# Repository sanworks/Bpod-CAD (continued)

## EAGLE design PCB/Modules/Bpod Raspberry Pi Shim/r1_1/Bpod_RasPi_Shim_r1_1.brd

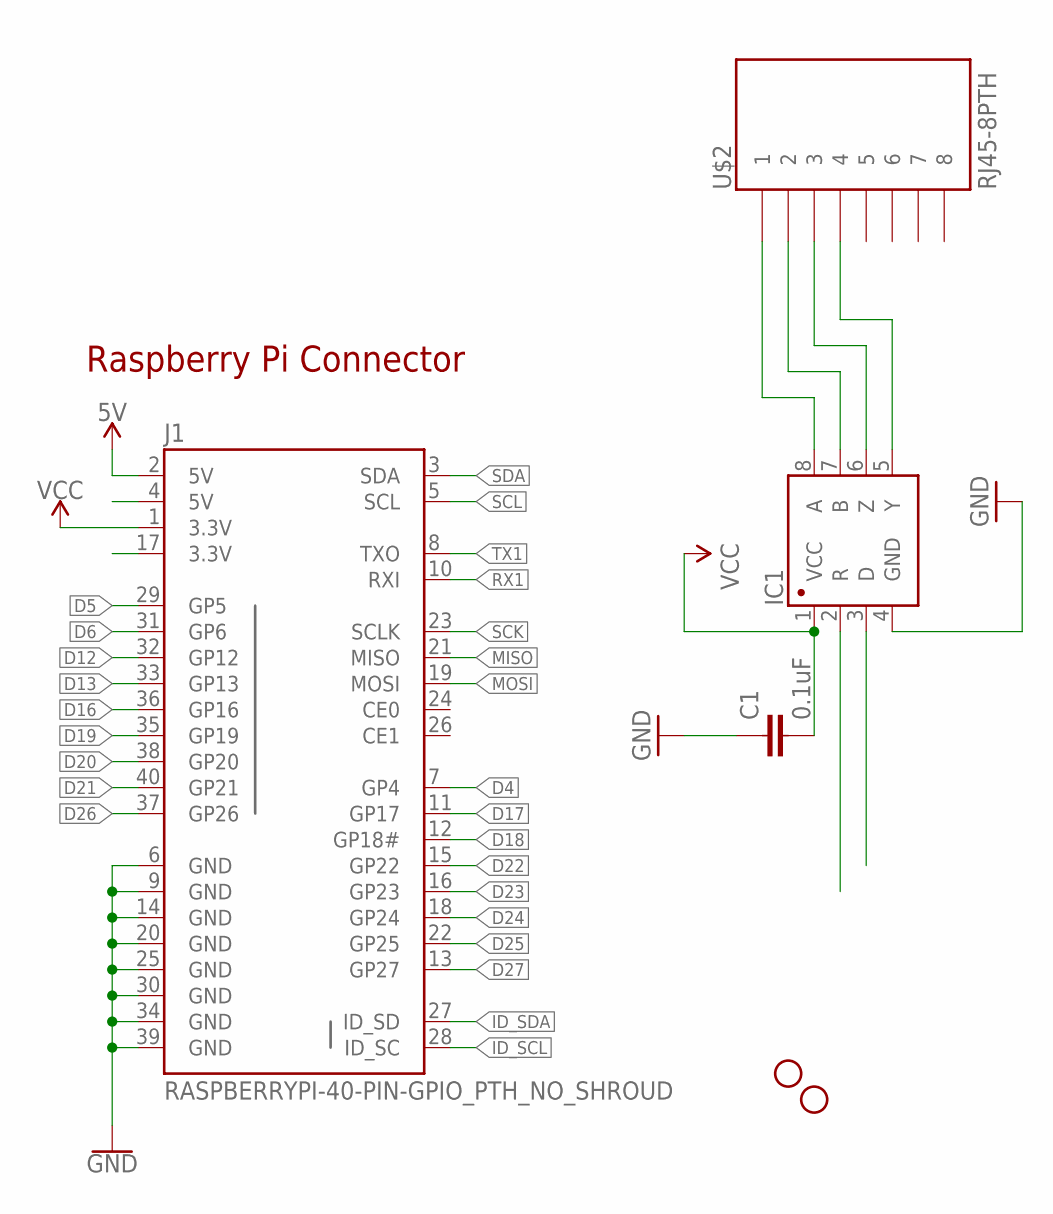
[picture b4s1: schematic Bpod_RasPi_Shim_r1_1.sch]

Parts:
C1: 0.1uF; 0805
H3, H4: STAND-OFFTIGHT; STAND-OFF-TIGHT
IC1: SN65HVD31DR; SO08
J1: RASPBERRYPI-40-PIN-GPIO_PTH_NO_SHROUD; 2X20
U$2: RJ45-8PTH; RJ45-8

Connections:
5V: J1.2 (5V)
D4: J1.7 (GP4)
D5: J1.29 (GP5)
D6: J1.31 (GP6)
D12: J1.32 (GP12)
D13: J1.33 (GP13)
D16: J1.36 (GP16)
D17: J1.11 (GP17)
D18: J1.12 (GP18#)
D19: J1.35 (GP19)
D20: J1.38 (GP20)
D21: J1.40 (GP21)
D22: J1.15 (GP22)
D23: J1.16 (GP23)
D24: J1.18 (GP24)
D25: J1.22 (GP25)
D26: J1.37 (GP26)
D27: J1.13 (GP27)
GND: C1.1, IC1.4 (GND), J1.6 (GND), J1.9 (GND), J1.14 (GND), J1.20 (GND), J1.25 (GND), J1.30 (GND), J1.34 (GND), J1.39 (GND)
ID_SCL: J1.28 (ID_SC)
ID_SDA: J1.27 (ID_SD)
MISO: J1.21 (MISO)
MOSI: J1.19 (MOSI)
unnamed: IC1.8 (A), U$2.1
unnamed: IC1.7 (B), U$2.2
unnamed: IC1.6 (Z), U$2.3
unnamed: IC1.5 (Y), U$2.4
RX1: IC1.2 (R), J1.10 (RXI)
SCK: J1.23 (SCLK)
SCL: J1.5 (SCL)
SDA: J1.3 (SDA)
TX1: IC1.3 (D), J1.8 (TXO)
VCC: C1.2, IC1.1 (VCC), J1.1 (3.3V)

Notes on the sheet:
Raspberry Pi Connector

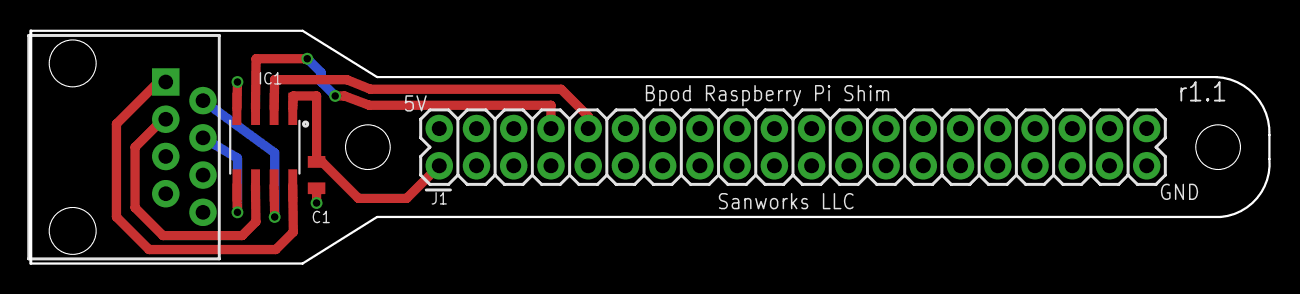
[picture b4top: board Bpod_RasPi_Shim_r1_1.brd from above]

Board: 2 copper layers, 84.5 x 15.9 mm, 6 parts (0 on the bottom side), 8 nets.

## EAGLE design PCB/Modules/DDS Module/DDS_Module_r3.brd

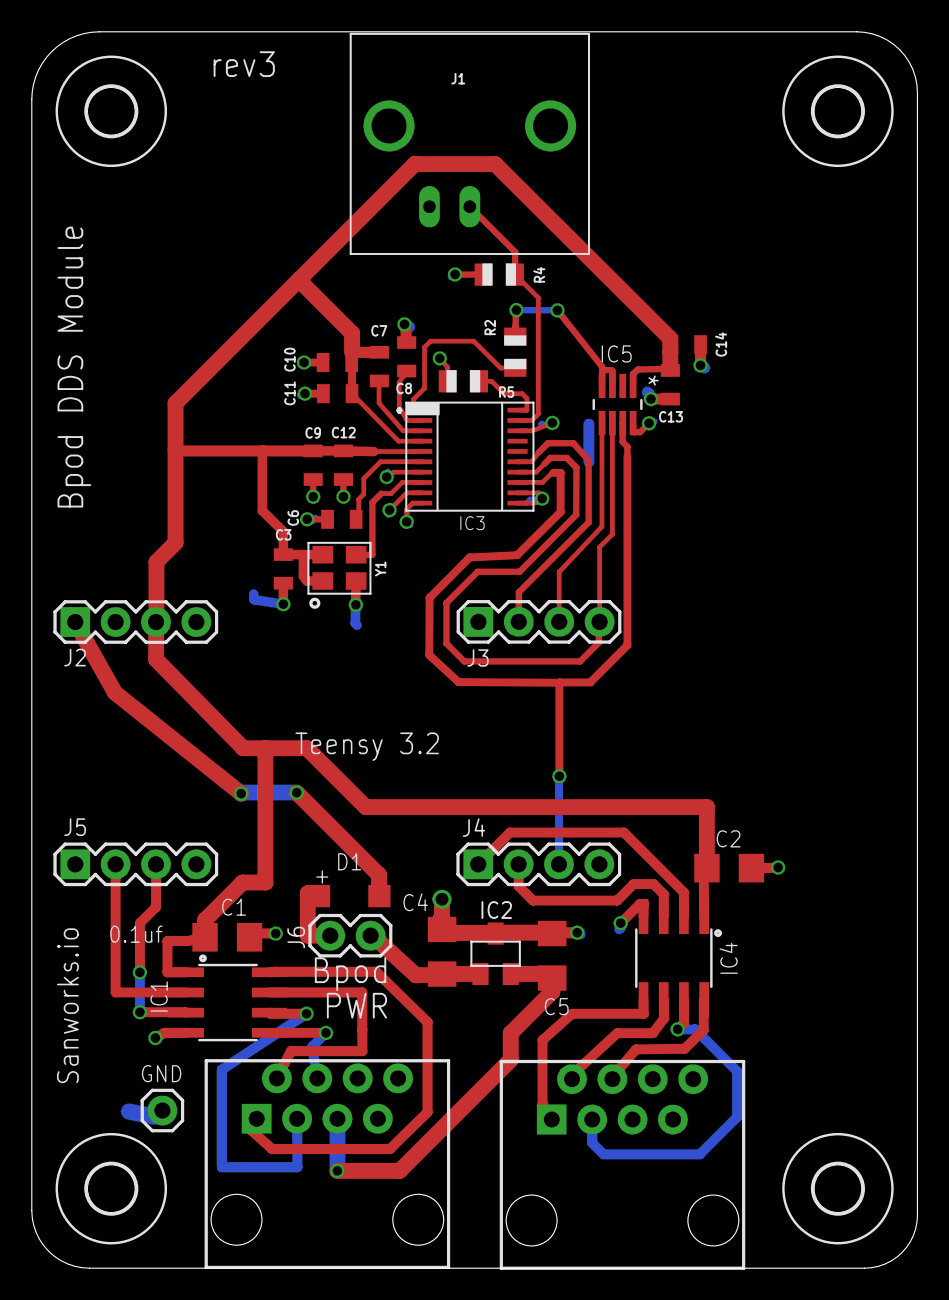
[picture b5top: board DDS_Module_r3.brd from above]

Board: 2 copper layers, 55.7 x 77.8 mm, 37 parts (0 on the bottom side), 30 nets.

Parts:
C1, C2, C4, C5: 0.1uf; 1206@1
C3, C7: 0.01uF; 0805
C6, C8, C11, C12, C13: 0.1uF; 0805
C9, C10, C14: 10uF; 0805
D1: MBR0520LT; SOD123
H1, H2, H3, H4: MOUNT-HOLE3.0; 3,0
IC1, IC4: SN65HVD31DR; SO08
IC2: LM3480-5.0; SOT-23-3
IC3: AD9834; TSSOP20
IC5: AD5620BRJZ-2500RL7; RJ_8
J1: BNCPTH; BNC
J2, J3, J4, J5: 1X04
J6: 1X02
J7: 1X01
R2: 6.8k; R0805
R4, R5: 200; R0805
U$1, U$3: RJ45-8PTH; RJ45-8
Y1: ASE10MHZ

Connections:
5V: D1.C, J2.1
GND: C1.2, C2.2, C3.1, C4.1, C5.1, C6.1, C8.2, C9.2, C10.2, C11.2, C12.2, C13.1, C14.2, IC1.4, IC2.3, IC3.7, IC3.9, IC3.10, IC3.11, IC3.12, IC3.18, IC4.4, IC5.8, J1.GND, J5.1, J7.1, R4.1, R5.1, U$1.6, Y1.P$2
unnamed: IC3.13, IC5.7, J4.3
unnamed: IC3.14, IC5.6, J3.4
unnamed: IC5.5, J3.3
unnamed: IC3.20, R5.2
unnamed: IC3.15, J3.2
unnamed: IC3.1, R2.1
unnamed: IC1.8, U$1.1
unnamed: IC1.7, U$1.2
unnamed: IC1.6, U$1.3
unnamed: IC1.5, U$1.4
unnamed: IC5.3, IC5.4, R2.2
unnamed: IC3.8, Y1.P$3
unnamed: IC3.19, J1.S, R4.2
unnamed: C4.2, IC2.1, J6.1
unnamed: C6.2, IC3.6
unnamed: C7.2, IC3.3
unnamed: C8.1, IC3.2
unnamed: D1.A, J6.2
unnamed: IC4.5, U$3.1
unnamed: IC4.6, U$3.2
unnamed: IC4.7, U$3.3
unnamed: C5.2, IC2.2, U$1.5
unnamed: IC4.8, U$3.4
RX1: IC1.2, J5.2
RX2: IC4.2, J4.1
TX1: IC1.3, J5.3
TX2: IC4.3, J4.2
VCC: C1.1, C2.1, C3.2, C7.1, C9.1, C10.1, C11.1, C12.1, C13.2, C14.1, IC1.1, IC3.4, IC3.5, IC4.1, IC5.1, J2.3, Y1.P$1, Y1.P$4

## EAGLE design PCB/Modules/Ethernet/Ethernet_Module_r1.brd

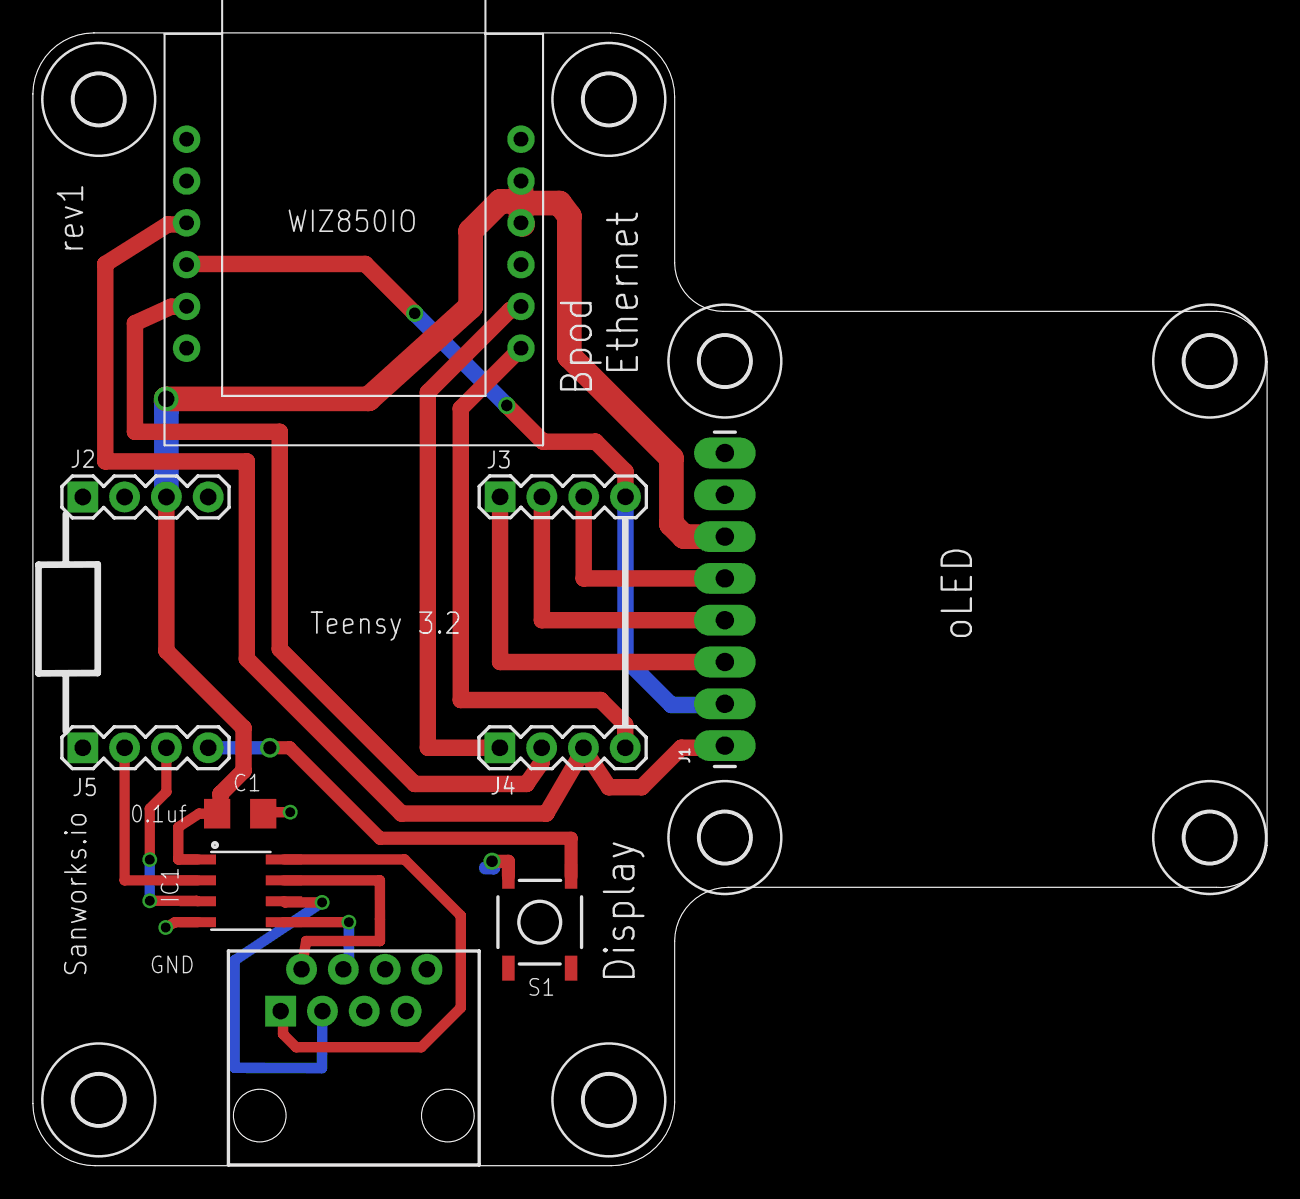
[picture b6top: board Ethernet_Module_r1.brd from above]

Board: 2 copper layers, 75.0 x 68.8 mm, 18 parts (0 on the bottom side), 17 nets.

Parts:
C1: 0.1uf; 1206@1
H1, H2, H3, H4, H5, H6, H7, H8: MOUNT-HOLE3.0; 3,0
IC1: SN65HVD31DR; SO08
J1: 1X08_LONGPADS
J2, J3, J4, J5: 1X04
S1: MOMENTARY-SWITCH-SPST-SMD-5.2MM; TACTILE_SWITCH_SMD_5.2MM
U$1: RJ45-8PTH; RJ45-8
WIZ850IO: WIZ850IO

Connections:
DC: J1.3, J3.1
ETH_CS: J4.2, WIZ850IO.P$5
ETH_RST: J4.1, WIZ850IO.P$8
GND: C1.2, IC1.4, J1.8, J5.1, S1.3, WIZ850IO.P$1, WIZ850IO.P$2, WIZ850IO.P$12
MISO: J4.4, WIZ850IO.P$7
MOSI: J1.1, J4.3, WIZ850IO.P$3
unnamed: J5.4, S1.1
unnamed: IC1.8, U$1.1
unnamed: IC1.7, U$1.2
unnamed: IC1.6, U$1.3
unnamed: IC1.5, U$1.4
OLED_CS: J1.5, J3.3
OLED_RST: J1.4, J3.2
RX1: IC1.2, J5.2
SCK: J1.2, J3.4, WIZ850IO.P$4
TX1: IC1.3, J5.3
VCC: C1.1, IC1.1, J1.6, J2.3, WIZ850IO.P$10, WIZ850IO.P$11
